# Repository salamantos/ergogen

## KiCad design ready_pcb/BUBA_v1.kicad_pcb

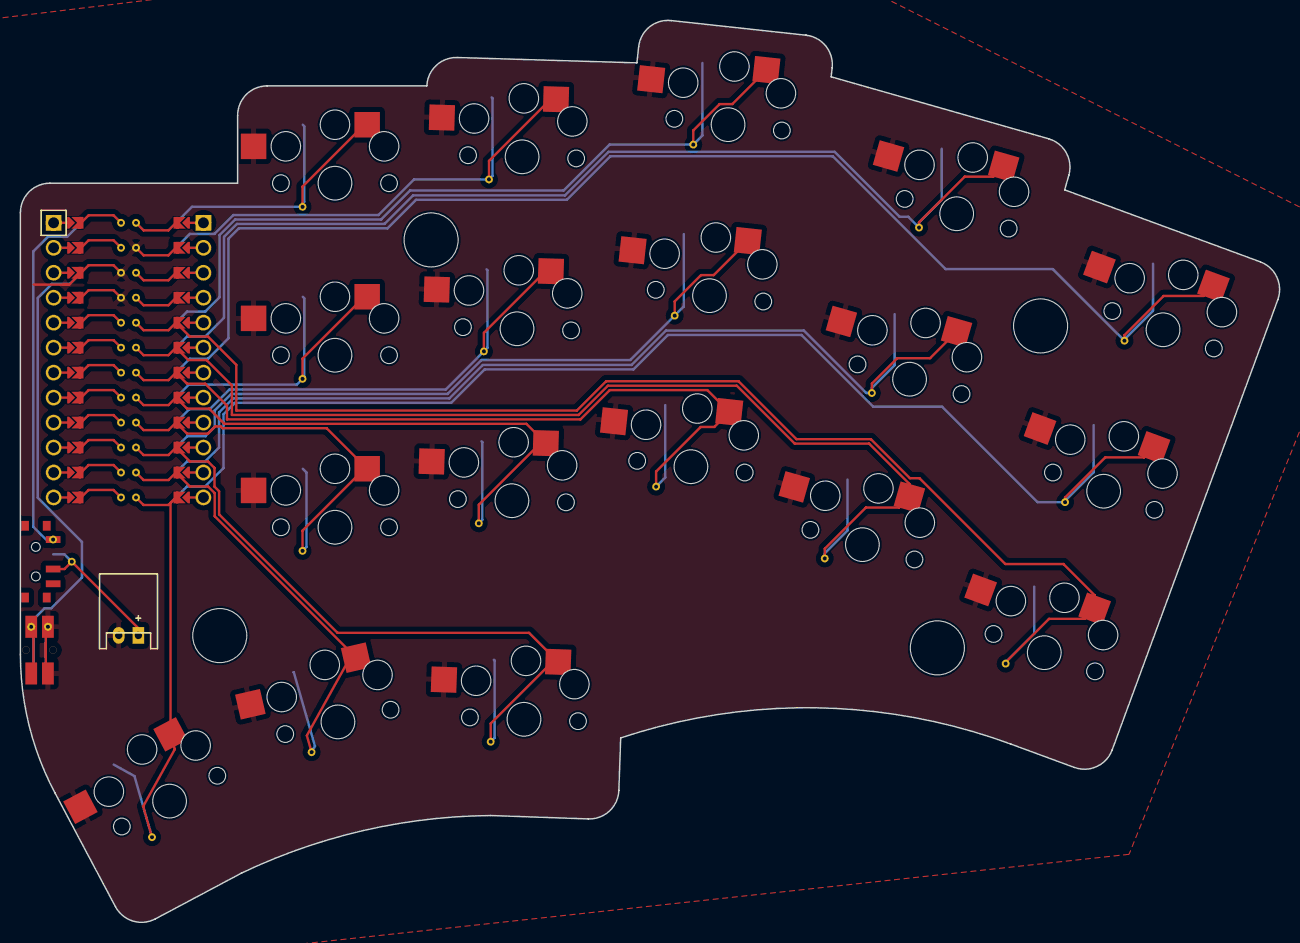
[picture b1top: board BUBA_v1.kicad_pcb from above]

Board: 2 copper layers, 128.1 x 91.7 mm, 21 parts (0 on the bottom side), 20 nets.

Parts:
BAT1: JST_PH_S2B-PH-K_02x2.00mm_Angled
MCU1: ProMicro
RST1: RST; YD-3414
S1, S2, S3, S4, S5, S6, S7, S8, S9, S10, S11, S12, S13, S14, S15, S16, S17, S18: PG1350

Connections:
GND: BAT1.2, MCU1.2, MCU1.21, MCU1.22, RST1.2, S1.2, S2.2, S3.2, S4.2, S5.2, S6.2, S7.2, S8.2, S9.2, S10.2, S11.2, S12.2, S13.2, S14.2, S15.2, S16.2, S17.2, S18.2
P0: MCU1.23, S6.1
P1: MCU1.24, S3.1
P2: MCU1.20, S9.1
P3: MCU1.19, S12.1
P4: MCU1.18, S15.1
P5: MCU1.17, S2.1
P6: MCU1.16, S5.1
P7: MCU1.15, S8.1
P8: MCU1.14, S11.1
P9: MCU1.13, S14.1
P10: MCU1.12, S17.1
P14: MCU1.10, S18.1
P15: MCU1.9, S1.1
P16: MCU1.11, S16.1
P18: MCU1.8, S4.1
P19: MCU1.7, S7.1
P20: MCU1.6, S10.1
P21: MCU1.5, S13.1
RST: MCU1.3, RST1.1

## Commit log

2024-07-27 BUBA v1 PCB
2024-07-31 add mounnting holes to outline
2024-12-18 add ready pcb
2024-12-18 gitignore
